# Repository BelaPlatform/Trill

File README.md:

# Trill: Touch Sensing for Makers

Trill sensors are designed to bring beautiful touch interaction to digital projects. Trill sensors are available now on the [Bela Shop](https://shop.bela.io/collections/trill) and via [Mouser Electronics](https://www.mouser.com/c/sensors/sensor-development-tools/?m=Bela).

## Trill libraries and examples

The Bela IDE comes pre-loaded with the [Trill library](https://github.com/BelaPlatform/Bela/tree/master/libraries/Trill) and [Trill examples](https://github.com/BelaPlatform/Bela/tree/master/examples/Trill).

For other platforms:

- [`Trill-Linux`](https://github.com/BelaPlatform/Trill-Linux) contains the Trill library and examples for Linux systems, such as Raspberry Pi

- [`Trill-Arduino`](https://github.com/BelaPlatform/Trill-Arduino) contains the Trill library and examples for Arduino, as well as Arduino-compatible systems such as Teensy. These also include examples of how to connect your Trill sensor to Processing to generate visuals.

## Trill hardware designs

This repo contains the editable PCB designs and manufacturing files for Trill sensors. You can download these schematic source and PCB design files and edit them yourself using [KiCad](https://www.kicad.org/).

### Source Files and Licenses

Trill hardware designs and this datasheet are available under a [Creative Commons Attribution-ShareAlike 4.0 International (CC BY-SA 4.0)](http://creativecommons.org/licenses/by-sa/4.0/) License, meaning they can be freely reused and remixed with attribution, provided modifications remain open source. Trill firmware is licensed under [GNU General Public License 3](https://www.gnu.org/licenses/gpl-3.0.html), meaning that you can freely use, remix, change and extend the code, but you are obligated to make the modified source code available alongside any binaries (flashed, or as files) that you release.

### Commercial Licensing

It's possible to use Trill design files and firmware for a commercial projects free of charge under [CC-BY-SA](http://creativecommons.org/licenses/by-sa/4.0/) (hardware) and [GPL](https://www.gnu.org/licenses/gpl-3.0.en.html) (firmware). Both licenses allow you to use these assets yourself under the license requirements, which include publicly releasing any changes you make to the designs under the same license.

If you want to use Trill design files but not provide attribution and/or not release your source code – for example, because you want to create something to sell using these files but don't want to make your source files public – this is still possible, but requires a commercial license. Augmented Instruments Ltd. can provide you with a commercial license that fits your project and its scope. Get in touch at info@bela.io to discuss your product and the license that's right for you. More information may be found at https://learn.bela.io/products/products-overview/open-source-licenses/#using-trill-in-commercial-products

Please note: The above commercial licensing applies only to modifications to our provided firmware code and PCB designs. You can buy Trill sensors and use them in any commercial or personal project without any additional licensing costs.

## Trill name and logo 

Trill and Bela names and logos are copyright Augmented Instruments Ltd. Any  designs that you release or produce should **not** use the Trill name or logo and/or the Bela name and logo, whether modified or exact copies.

## Datasheet

This repo contains the Trill datasheet. There is one datasheet for all Trill sensors that includes technical diagrams and usage information. 

## Fritzing files

Fritzing parts are available for all Trill sensors, in the [Bela Fritzing repo](https://github.com/belaplatform/fritzing).

## Learn more

The Bela Knowledge Base contains great documentation on using Trill! Visit [learn.bela.io/trill](https://learn.bela.io/trill) for more information, as well as our Get Started Guide.

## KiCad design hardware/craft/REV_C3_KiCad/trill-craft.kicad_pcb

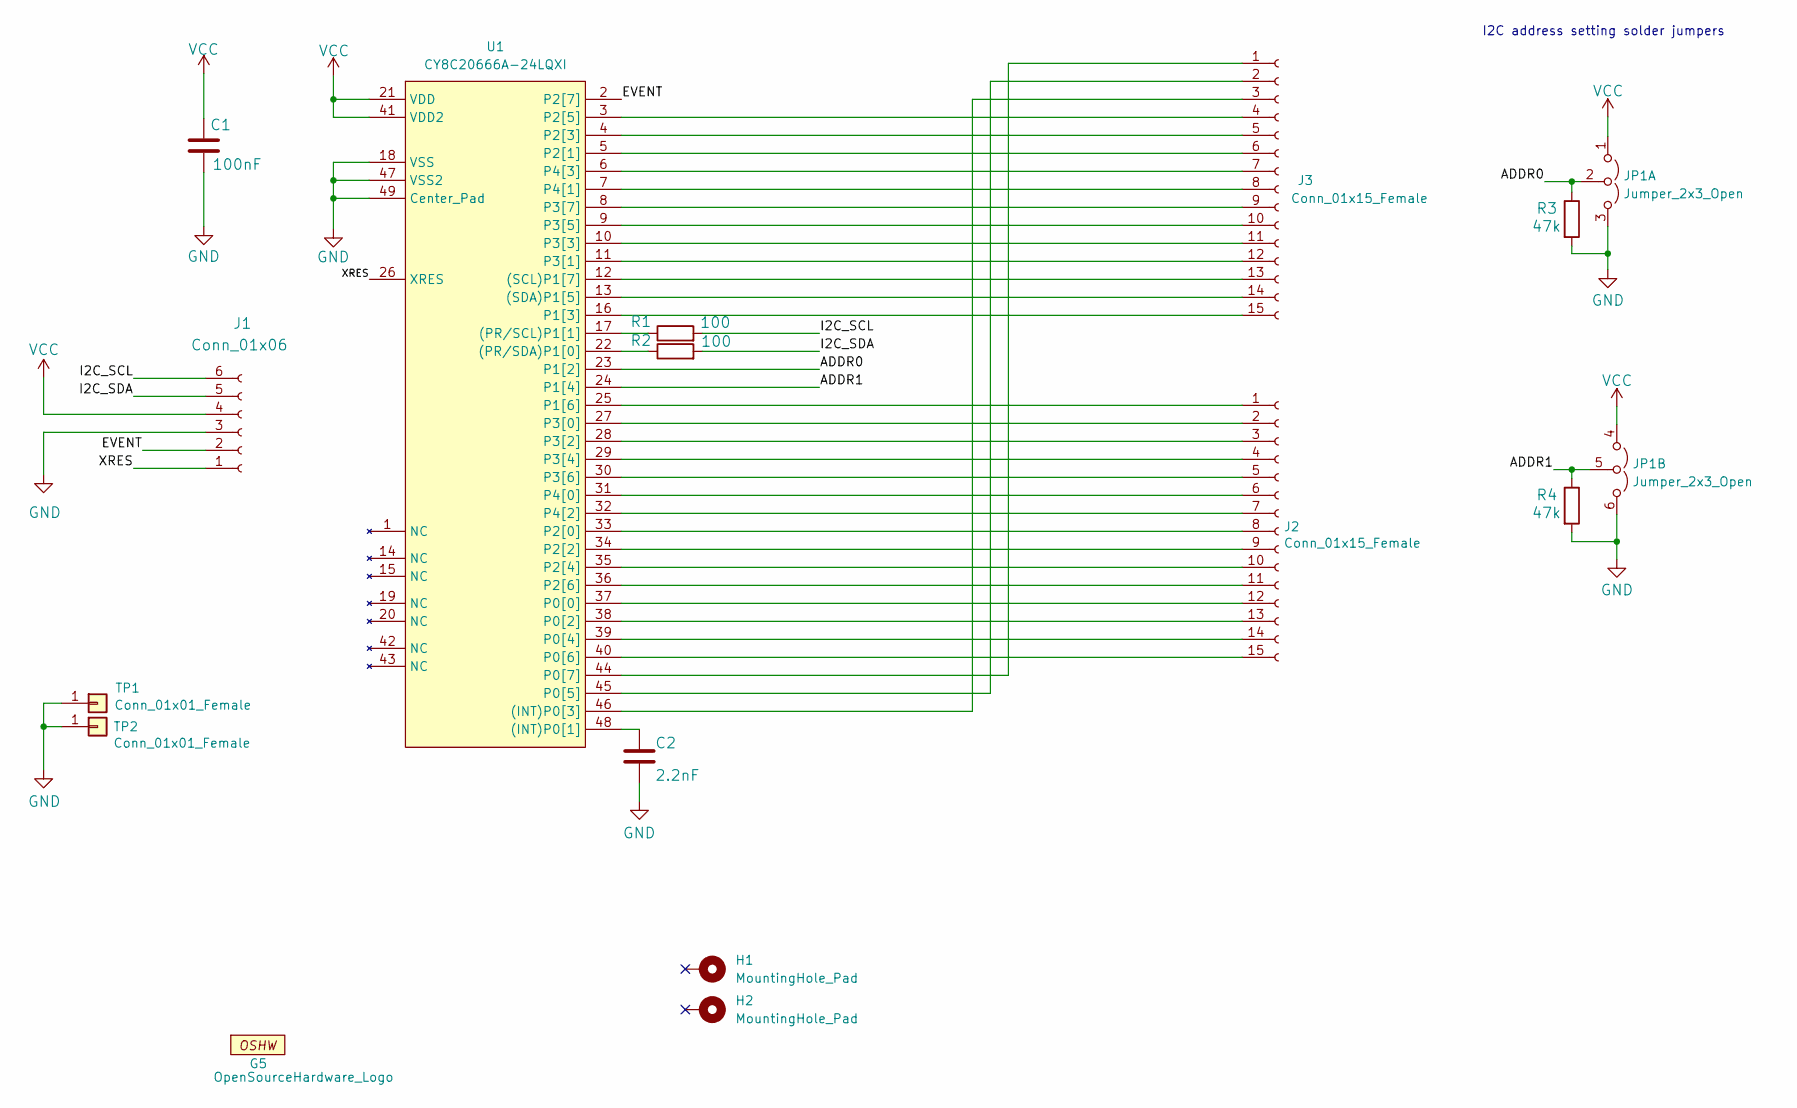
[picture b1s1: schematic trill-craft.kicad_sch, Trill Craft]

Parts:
C1: 100nF; C_0402_1005Metric
C2: 2.2nF; C_0402_1005Metric
G5: OpenSourceHardware_Logo
H1, H2: MountingHole_Pad; MountingHole_3.2mm_M3_ISO14580_Pad
J1: Conn_01x06; trill_craft_1X6_2.54mm_castelated_round
J2, J3: Conn_01x15_Female; trill_craft_1x15_2.54mm_castellated_round
JP1: Jumper_2x3_Open; SolderJumper-2x3_P1.3mm_Open_Pad1.0x1.5mm
R1, R2: 100; R_0402_1005Metric
R3, R4: 47k; R_0402_1005Metric
TP1, TP2: Conn_01x01_Female; trill_craft_circular_pad_smd
U1: CY8C20666A-24LQXI; QFN-48-1EP_6x6mm_P0.4mm_EP4.6x4.6mm

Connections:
/ADDR0: JP1.2 (C), R3.1, U1.23 (P1[2])
/ADDR1: JP1.5 (A), R4.1, U1.24 (P1[4])
/EVENT: J1.2, U1.2 (P2[7])
/I2C_SCL: J1.6, R1.2
/I2C_SDA: J1.5, R2.2
/XRES: J1.1, U1.26 (XRES)
GND: C1.1, C2.2, J1.3, JP1.3 (B), JP1.6 (B), R3.2, R4.2, TP1.1, TP2.1, U1.18 (VSS), U1.47 (VSS2), U1.49 (Center_Pad)
unnamed: J2.1, U1.25 (P1[6])
unnamed: J2.2, U1.27 (P3[0])
unnamed: J2.3, U1.28 (P3[2])
unnamed: J2.4, U1.29 (P3[4])
unnamed: J2.5, U1.30 (P3[6])
unnamed: J2.6, U1.31 (P4[0])
unnamed: J2.7, U1.32 (P4[2])
unnamed: J2.8, U1.33 (P2[0])
unnamed: J2.9, U1.34 (P2[2])
unnamed: J2.10, U1.35 (P2[4])
unnamed: J2.11, U1.36 (P2[6])
unnamed: J2.12, U1.37 (P0[0])
unnamed: J2.13, U1.38 (P0[2])
unnamed: J2.14, U1.39 (P0[4])
unnamed: J2.15, U1.40 (P0[6])
unnamed: J3.1, U1.44 (P0[7])
unnamed: J3.2, U1.45 (P0[5])
unnamed: J3.3, U1.46 ((INT)P0[3])
unnamed: J3.4, U1.3 (P2[5])
unnamed: J3.5, U1.4 (P2[3])
unnamed: J3.6, U1.5 (P2[1])
unnamed: J3.7, U1.6 (P4[3])
unnamed: J3.8, U1.7 (P4[1])
unnamed: J3.9, U1.8 (P3[7])
unnamed: J3.10, U1.9 (P3[5])
unnamed: J3.11, U1.10 (P3[3])
unnamed: J3.12, U1.11 (P3[1])
unnamed: J3.13, U1.12 ((SCL)P1[7])
unnamed: J3.14, U1.13 ((SDA)P1[5])
unnamed: J3.15, U1.16 (P1[3])
unnamed: C2.1, U1.48 ((INT)P0[1])
unnamed: R1.1, U1.17 ((PR/SCL)P1[1])
unnamed: R2.1, U1.22 ((PR/SDA)P1[0])
VCC: C1.2, J1.4, JP1.1 (A), JP1.4 (A), U1.21 (VDD), U1.41 (VDD2)

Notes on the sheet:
I2C address setting solder jumpers

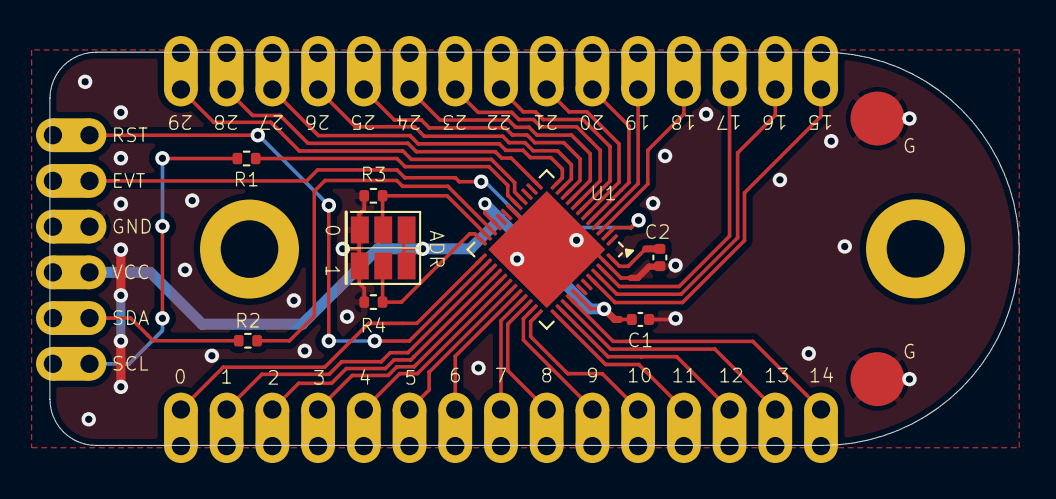
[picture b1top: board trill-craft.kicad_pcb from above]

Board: 2 copper layers, 53.8 x 21.8 mm, 16 parts (1 on the bottom side), 41 nets.

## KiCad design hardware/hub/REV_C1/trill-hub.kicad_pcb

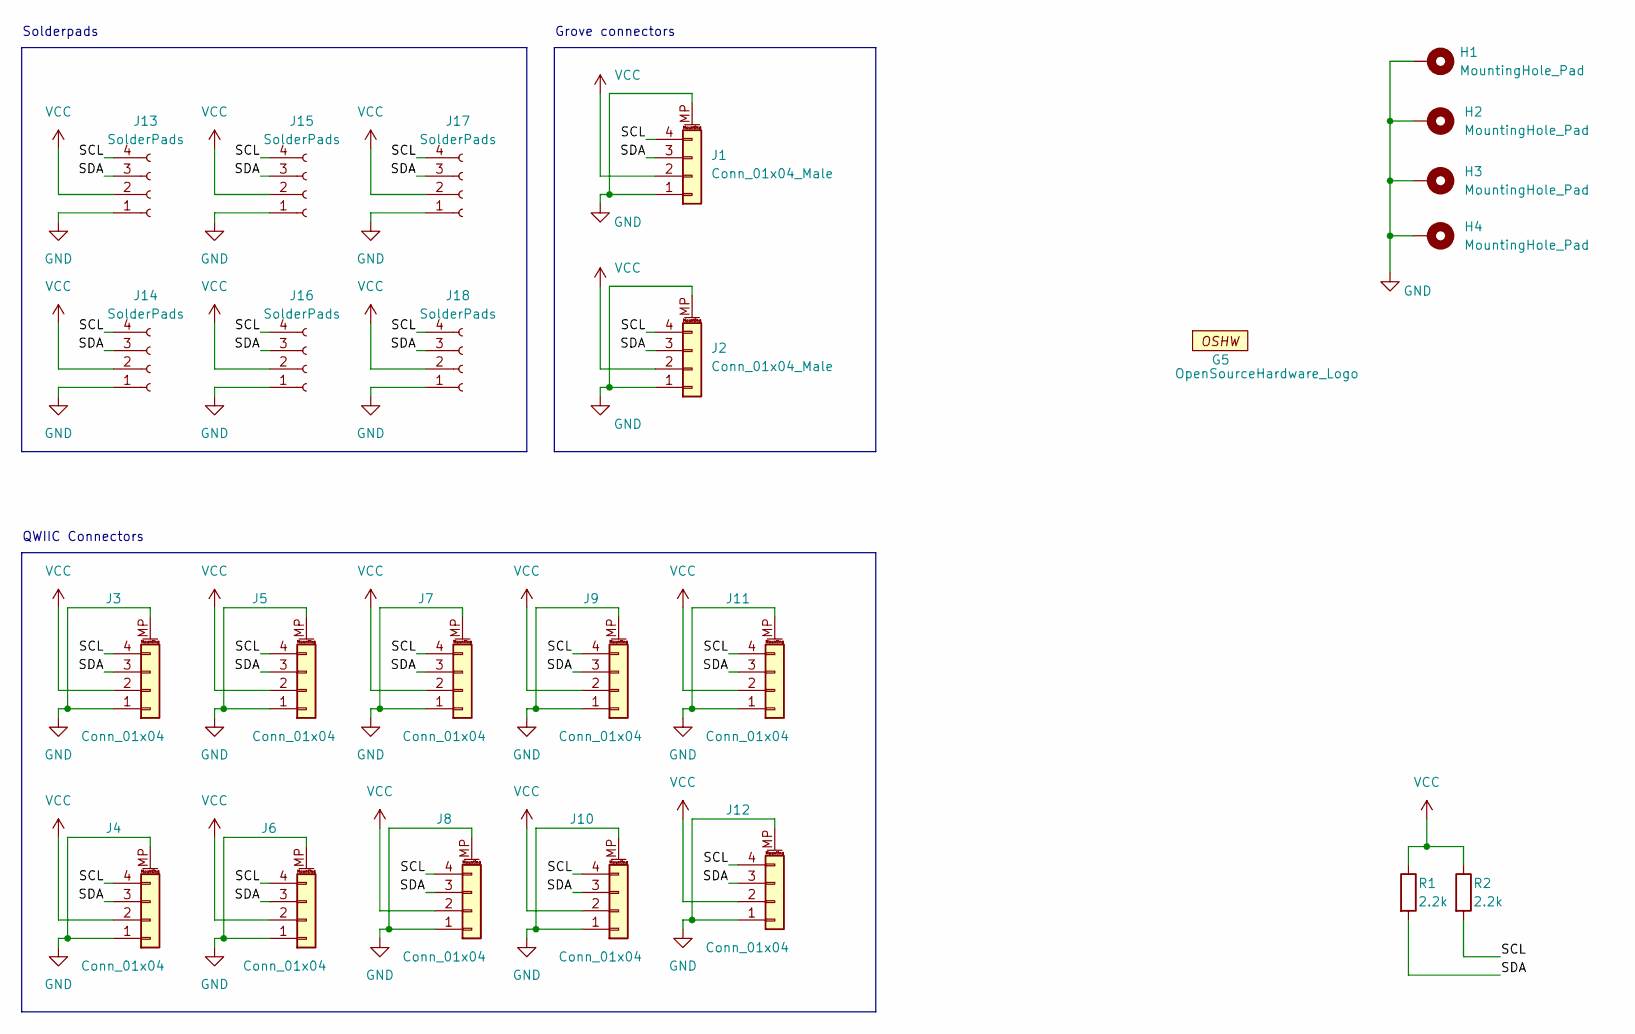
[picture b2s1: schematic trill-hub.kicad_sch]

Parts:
G5: OpenSourceHardware_Logo
H1, H2, H3, H4: MountingHole_Pad; MountingHole_3.2mm_M3_ISO14580_Pad
J1, J2: Conn_01x04_Male; JST_PH_B4B-PH-SM4-TB_1x04-1MP_P2.00mm_Vertical
J3, J4, J5, J6, J7, J8, J9, J10, J11, J12: Conn_01x04; qwiic_vertical_SMD
J13, J14, J15, J16, J17, J18: SolderPads; Connector_1x04_LongPads
R1, R2: 2.2k; R_0402_1005Metric

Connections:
/SCL: J1.4, J2.4, J3.4, J4.4, J5.4, J6.4, J7.4, J8.4, J9.4, J10.4, J11.4, J12.4, J13.4, J14.4, J15.4, J16.4, J17.4, J18.4, R2.2
/SDA: J1.3, J2.3, J3.3, J4.3, J5.3, J6.3, J7.3, J8.3, J9.3, J10.3, J11.3, J12.3, J13.3, J14.3, J15.3, J16.3, J17.3, J18.3, R1.2
GND: H1.1, H2.1, H3.1, H4.1, J1.1, J1.MP (MountPin), J2.1, J2.MP (MountPin), J3.1, J3.MP (MountPin), J4.1, J4.MP (MountPin), J5.1, J5.MP (MountPin), J6.1, J6.MP (MountPin), J7.1, J7.MP (MountPin), J8.1, J8.MP (MountPin), J9.1, J9.MP (MountPin), J10.1, J10.MP (MountPin), J11.1, J11.MP (MountPin), J12.1, J12.MP (MountPin), J13.1, J14.1, J15.1, J16.1, J17.1, J18.1
VCC: J1.2, J2.2, J3.2, J4.2, J5.2, J6.2, J7.2, J8.2, J9.2, J10.2, J11.2, J12.2, J13.2, J14.2, J15.2, J16.2, J17.2, J18.2, R1.1, R2.1

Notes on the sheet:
Solderpads
QWIIC Connectors
Grove connectors

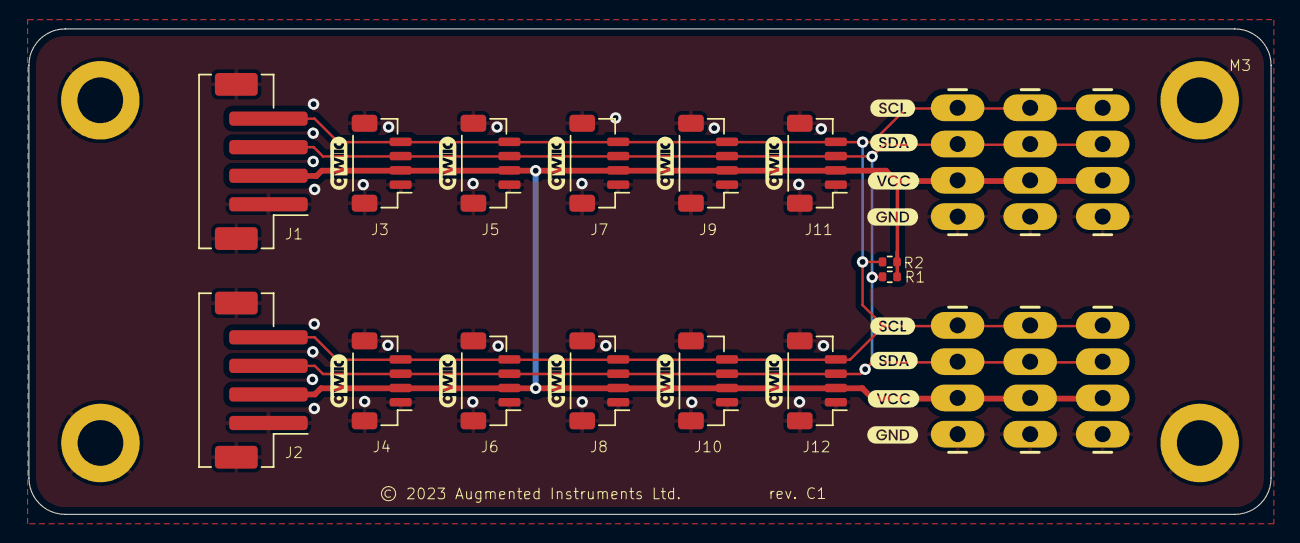
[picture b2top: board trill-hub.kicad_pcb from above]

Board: 2 copper layers, 87.0 x 34.0 mm, 25 parts (1 on the bottom side), 4 nets.

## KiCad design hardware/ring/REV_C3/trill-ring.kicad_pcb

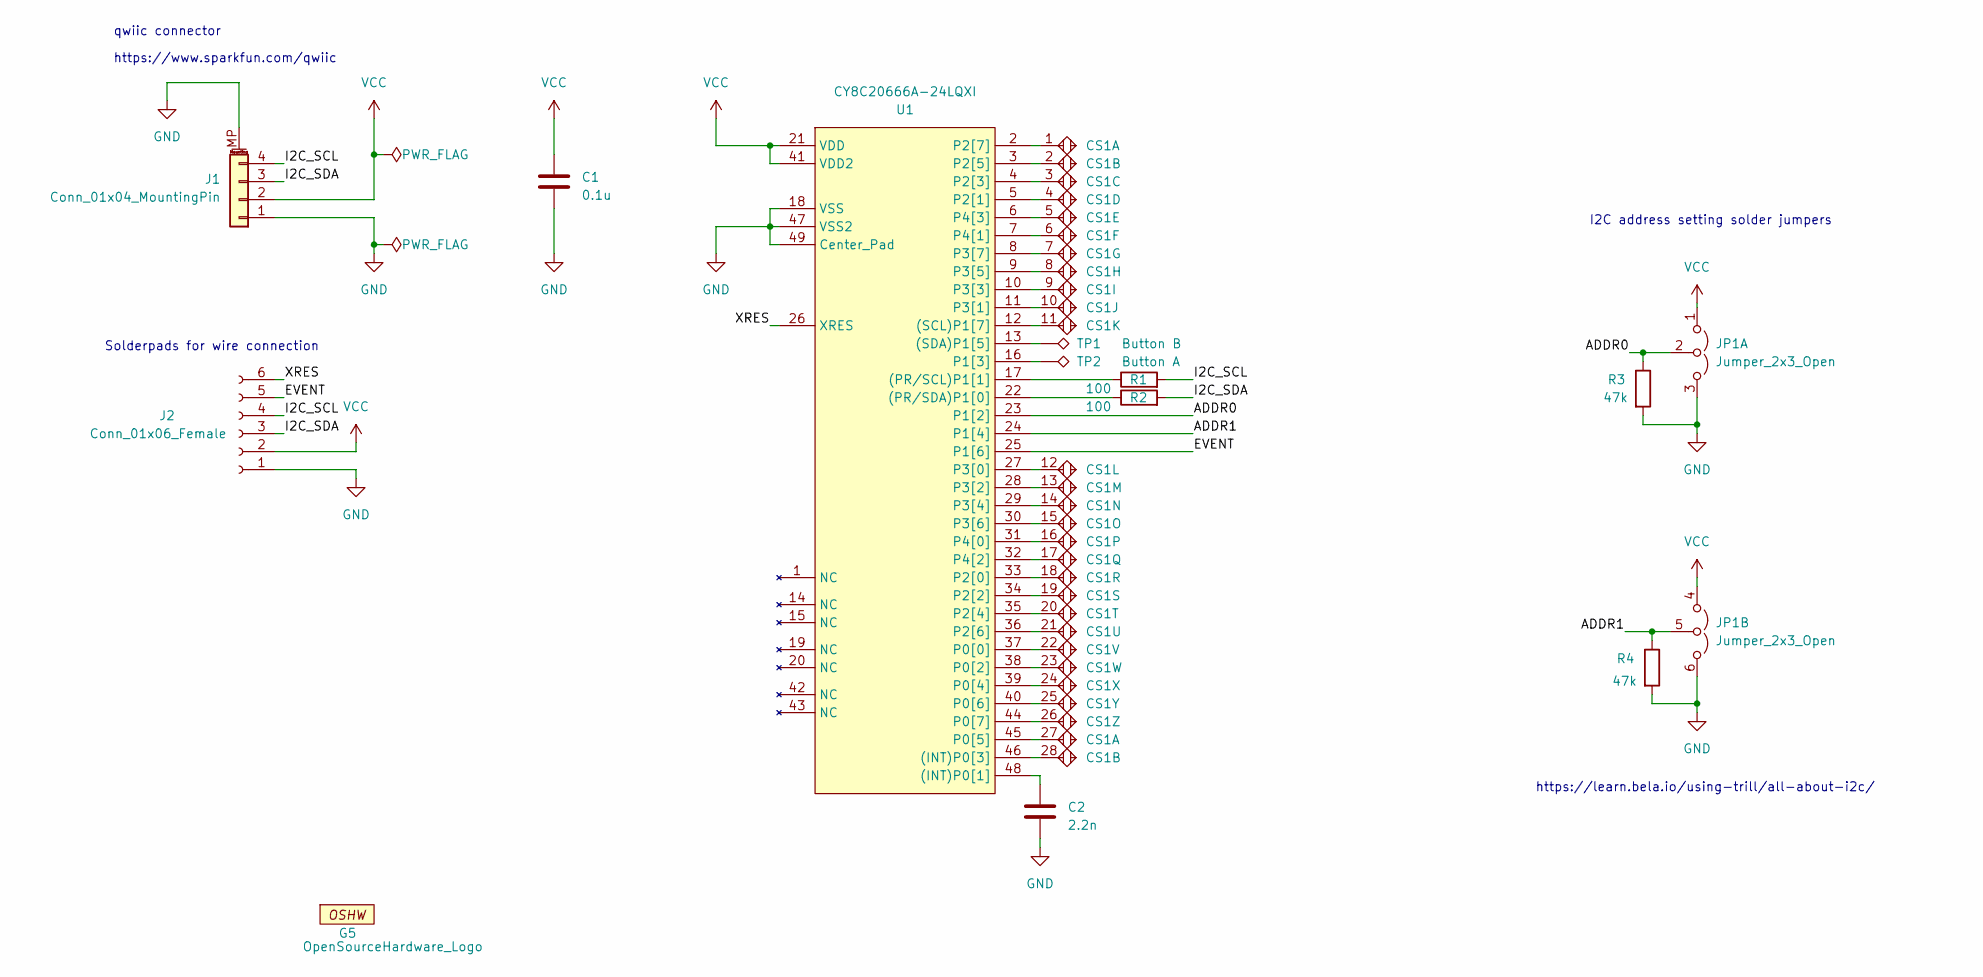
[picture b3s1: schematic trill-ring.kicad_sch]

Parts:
C1: 0.1u; C_0402_1005Metric
C2: 2.2n; C_0402_1005Metric
CS1: TRILL_RING-28_CapSense; TRILL_RING_CapSense
G5: OpenSourceHardware_Logo
J1: Conn_01x04_MountingPin; qwiic_horizontal_SMD
J2: Conn_01x06_Female; I2C+EVT_RST_Wire_connector_SMD
JP1: Jumper_2x3_Open; SolderJumper-2x3_P1.3mm_Open_Pad1.0x1.5mm
R1, R2: 100; R_0402_1005Metric
R3, R4: 47k; R_0402_1005Metric
TP1: Button B; TestPoint_Pad_D2.0mm
TP2: Button A; TestPoint_Pad_D2.0mm
U1: CY8C20666A-24LQXI; QFN-48-1EP_6x6mm_P0.4mm_EP4.6x4.6mm

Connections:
/ADDR0: JP1.2 (C), R3.1, U1.23 (P1[2])
/ADDR1: JP1.5 (A), R4.1, U1.24 (P1[4])
/EVENT: J2.5, U1.25 (P1[6])
/I2C_SCL: J1.4, J2.4, R1.2
/I2C_SDA: J1.3, J2.3, R2.2
/XRES: J2.6, U1.26 (XRES)
GND: C1.2, C2.2, J1.1, J1.MP (MountPin), J2.1, JP1.3 (B), JP1.6 (B), R3.2, R4.2, U1.18 (VSS), U1.47 (VSS2), U1.49 (Center_Pad)
unnamed: C2.1, U1.48 ((INT)P0[1])
unnamed: CS1.28, U1.46 ((INT)P0[3])
unnamed: R1.1, U1.17 ((PR/SCL)P1[1])
unnamed: R2.1, U1.22 ((PR/SDA)P1[0])
unnamed: CS1.11, U1.12 ((SCL)P1[7])
unnamed: TP1.1, U1.13 ((SDA)P1[5])
unnamed: CS1.22, U1.37 (P0[0])
unnamed: CS1.23, U1.38 (P0[2])
unnamed: CS1.24, U1.39 (P0[4])
unnamed: CS1.27, U1.45 (P0[5])
unnamed: CS1.25, U1.40 (P0[6])
unnamed: CS1.26, U1.44 (P0[7])
unnamed: TP2.1, U1.16 (P1[3])
unnamed: CS1.18, U1.33 (P2[0])
unnamed: CS1.4, U1.5 (P2[1])
unnamed: CS1.19, U1.34 (P2[2])
unnamed: CS1.3, U1.4 (P2[3])
unnamed: CS1.20, U1.35 (P2[4])
unnamed: CS1.2, U1.3 (P2[5])
unnamed: CS1.21, U1.36 (P2[6])
unnamed: CS1.1, U1.2 (P2[7])
unnamed: CS1.12, U1.27 (P3[0])
unnamed: CS1.10, U1.11 (P3[1])
unnamed: CS1.13, U1.28 (P3[2])
unnamed: CS1.9, U1.10 (P3[3])
unnamed: CS1.14, U1.29 (P3[4])
unnamed: CS1.8, U1.9 (P3[5])
unnamed: CS1.15, U1.30 (P3[6])
unnamed: CS1.7, U1.8 (P3[7])
unnamed: CS1.16, U1.31 (P4[0])
unnamed: CS1.6, U1.7 (P4[1])
unnamed: CS1.17, U1.32 (P4[2])
unnamed: CS1.5, U1.6 (P4[3])
VCC: C1.1, J1.2, J2.2, JP1.1 (A), JP1.4 (A), U1.21 (VDD), U1.41 (VDD2)

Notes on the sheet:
I2C address setting solder jumpers
qwiic connector
Solderpads for wire connection
https://learn.bela.io/using-trill/all-about-i2c/
https://www.sparkfun.com/qwiic

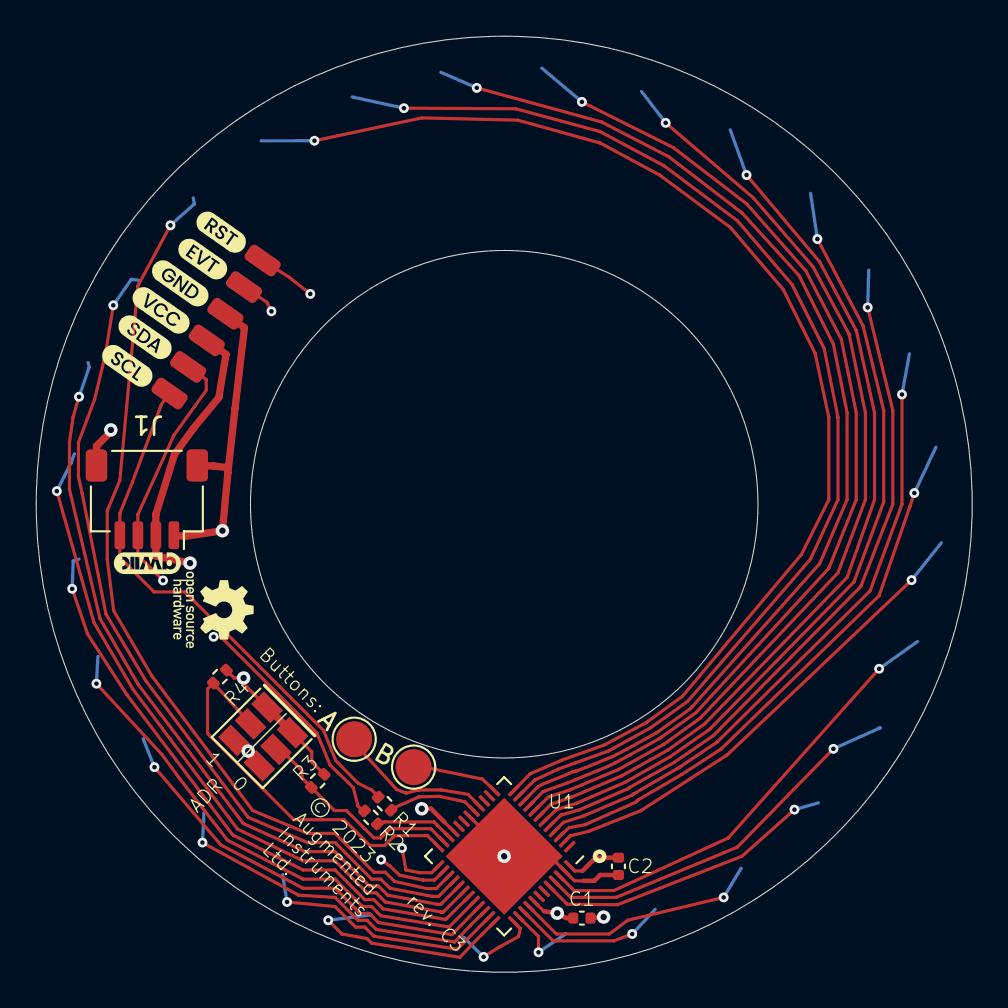
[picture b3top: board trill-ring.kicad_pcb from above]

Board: 4 copper layers, 52.0 x 52.0 mm, 14 parts (0 on the bottom side), 41 nets.

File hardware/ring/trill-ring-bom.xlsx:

Name | Quantity | Value | Package | Description | Mouser # | Digi-Key # | Datasheet / Notes
C1 | 1 | 0.1uF | “0402" | Capacitor ceramic 0402; standard bypass cap 5V+
C2 | 1 | 2.2nF | “0402" | Capacitor ceramic 0402; 5% | 81-GRM36X222J50
IC1 | 1 | CY8C20636A-24LTXI | 48-QFN, 7x7mm | IC Cypress SoC | 727-CY8C20636A24LTXI
J1 | 1 | Grove connector, vertical SMT | SMD | 4-pin 2mm vertical Grove connector (Seeed)
R1-R2 | 2 | 100 ohm | “0402" | Resistor 0603 (standard part)
R3-R4 | 2 | 47k ohm | “0402" | Resistor 0603 (standard part)
Total | 8

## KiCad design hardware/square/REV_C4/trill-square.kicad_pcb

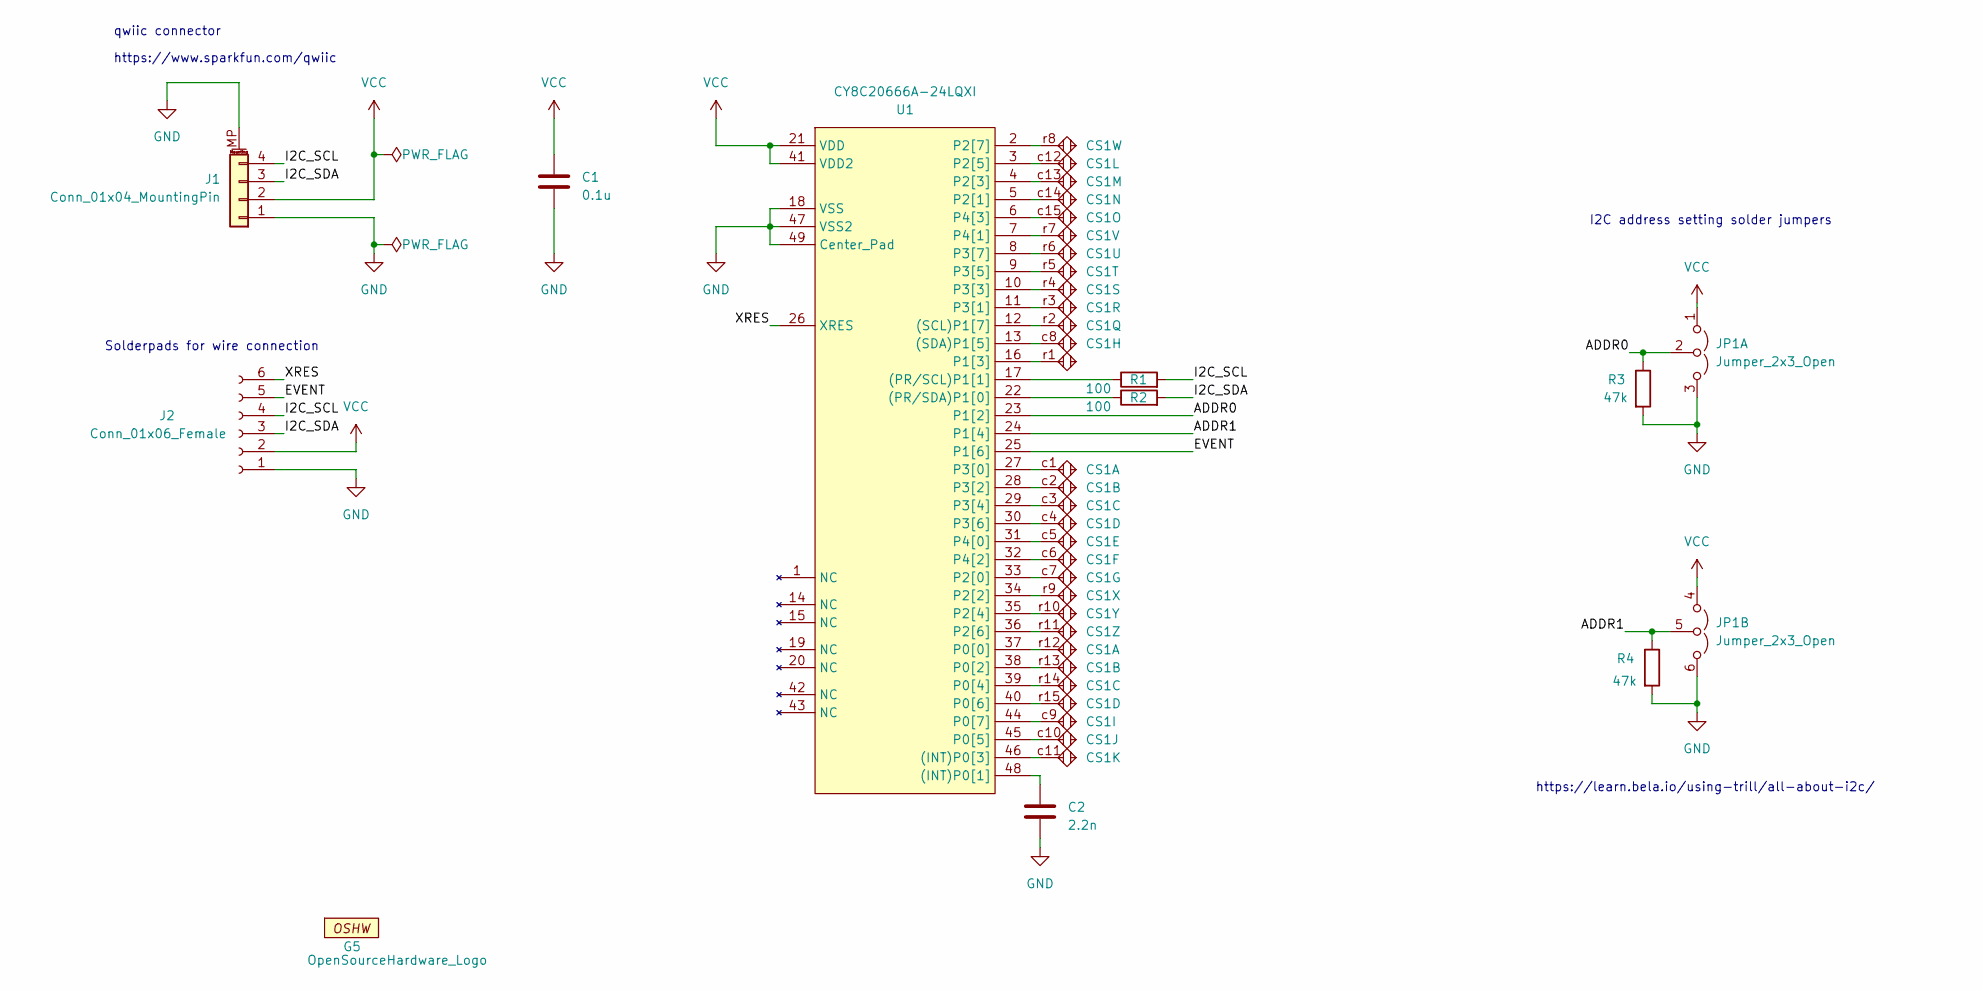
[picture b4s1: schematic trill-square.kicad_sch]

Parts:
C1: 0.1u; C_0402_1005Metric
C2: 2.2n; C_0402_1005Metric
CS1: CapSensePad; TRILL_SQUARE_CapSense
G5: OpenSourceHardware_Logo
J1: Conn_01x04_MountingPin; qwiic_horizontal_SMD
J2: Conn_01x06_Female; I2C+EVT_RST_Wire_connector_SMD
JP1: Jumper_2x3_Open; SolderJumper-2x3_P1.3mm_Open_Pad1.0x1.5mm
R1, R2: 100; R_0402_1005Metric
R3, R4: 47k; R_0402_1005Metric
U1: CY8C20666A-24LQXI; QFN-48-1EP_6x6mm_P0.4mm_EP4.6x4.6mm

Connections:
/ADDR0: JP1.2 (C), R3.1, U1.23 (P1[2])
/ADDR1: JP1.5 (A), R4.1, U1.24 (P1[4])
/EVENT: J2.5, U1.25 (P1[6])
/I2C_SCL: J1.4, J2.4, R1.2
/I2C_SDA: J1.3, J2.3, R2.2
/XRES: J2.6, U1.26 (XRES)
GND: C1.2, C2.2, J1.1, J1.MP (MountPin), J2.1, JP1.3 (B), JP1.6 (B), R3.2, R4.2, U1.18 (VSS), U1.47 (VSS2), U1.49 (Center_Pad)
unnamed: C2.1, U1.48 ((INT)P0[1])
unnamed: CS1.c11, U1.46 ((INT)P0[3])
unnamed: R1.1, U1.17 ((PR/SCL)P1[1])
unnamed: R2.1, U1.22 ((PR/SDA)P1[0])
unnamed: CS1.r2, U1.12 ((SCL)P1[7])
unnamed: CS1.c8, U1.13 ((SDA)P1[5])
unnamed: CS1.r12, U1.37 (P0[0])
unnamed: CS1.r13, U1.38 (P0[2])
unnamed: CS1.r14, U1.39 (P0[4])
unnamed: CS1.c10, U1.45 (P0[5])
unnamed: CS1.r15, U1.40 (P0[6])
unnamed: CS1.c9, U1.44 (P0[7])
unnamed: CS1.r1, U1.16 (P1[3])
unnamed: CS1.c7, U1.33 (P2[0])
unnamed: CS1.c14, U1.5 (P2[1])
unnamed: CS1.r9, U1.34 (P2[2])
unnamed: CS1.c13, U1.4 (P2[3])
unnamed: CS1.r10, U1.35 (P2[4])
unnamed: CS1.c12, U1.3 (P2[5])
unnamed: CS1.r11, U1.36 (P2[6])
unnamed: CS1.r8, U1.2 (P2[7])
unnamed: CS1.c1, U1.27 (P3[0])
unnamed: CS1.r3, U1.11 (P3[1])
unnamed: CS1.c2, U1.28 (P3[2])
unnamed: CS1.r4, U1.10 (P3[3])
unnamed: CS1.c3, U1.29 (P3[4])
unnamed: CS1.r5, U1.9 (P3[5])
unnamed: CS1.c4, U1.30 (P3[6])
unnamed: CS1.r6, U1.8 (P3[7])
unnamed: CS1.c5, U1.31 (P4[0])
unnamed: CS1.r7, U1.7 (P4[1])
unnamed: CS1.c6, U1.32 (P4[2])
unnamed: CS1.c15, U1.6 (P4[3])
VCC: C1.1, J1.2, J2.2, JP1.1 (A), JP1.4 (A), U1.21 (VDD), U1.41 (VDD2)

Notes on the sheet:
Solderpads for wire connection
qwiic connector
https://www.sparkfun.com/qwiic
https://learn.bela.io/using-trill/all-about-i2c/
I2C address setting solder jumpers

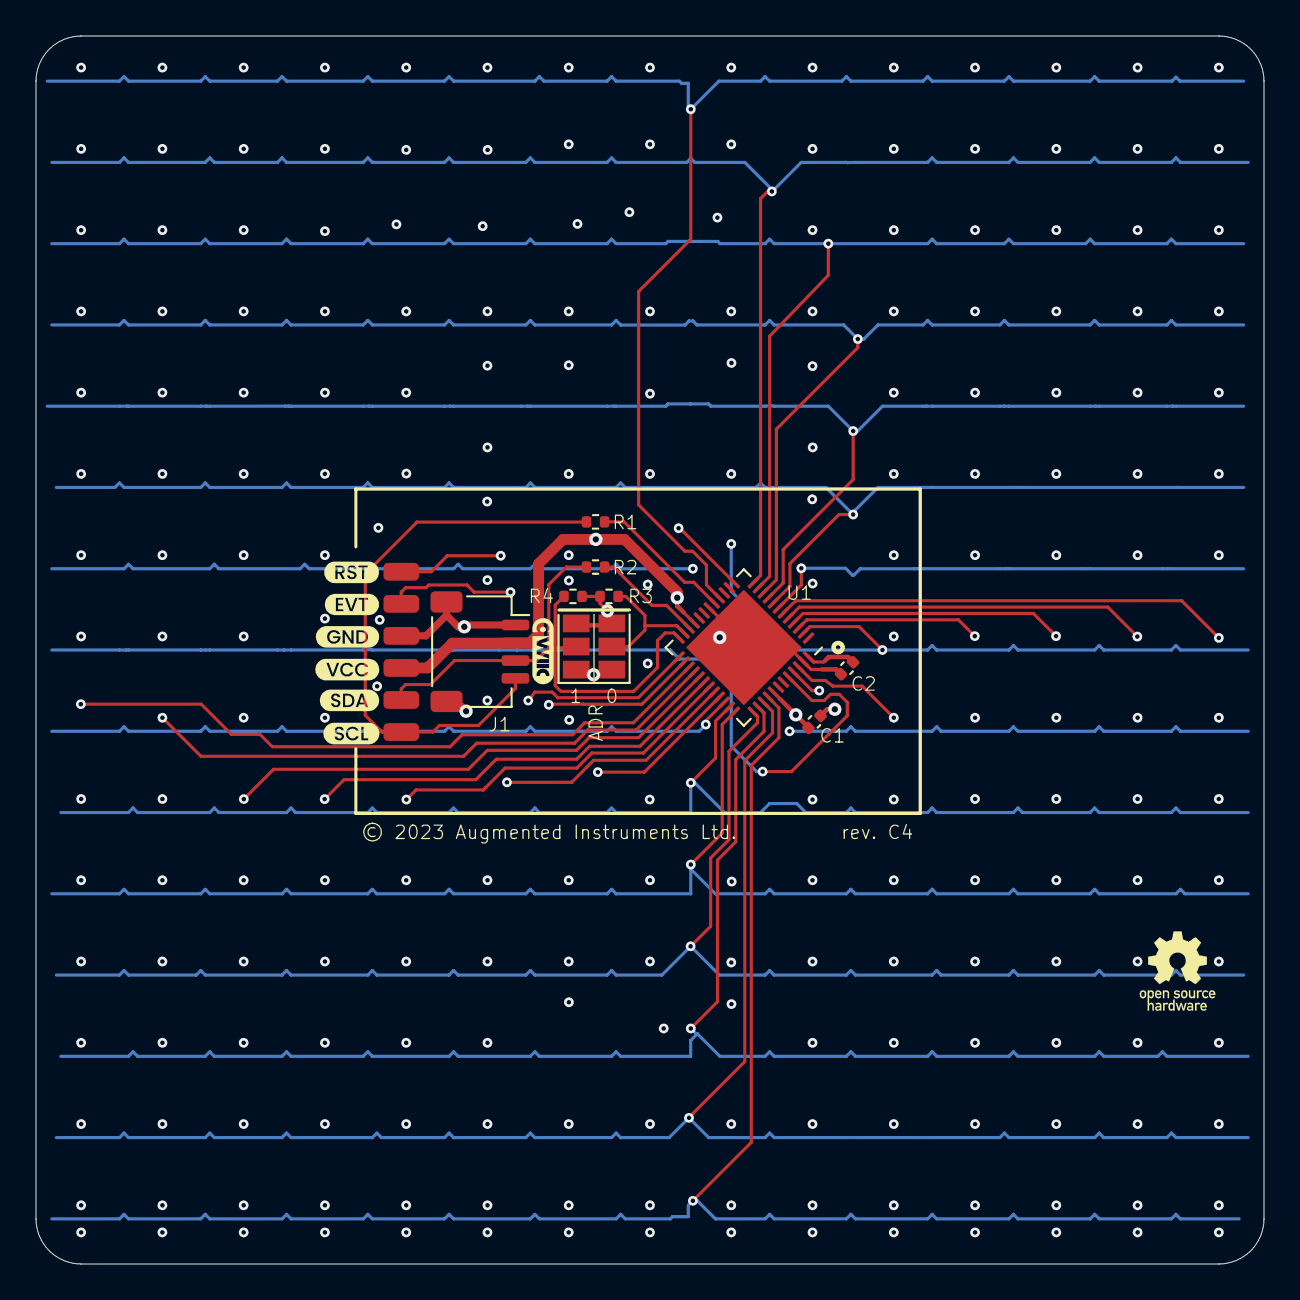
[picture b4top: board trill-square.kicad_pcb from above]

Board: 4 copper layers, 69.1 x 69.1 mm, 12 parts (0 on the bottom side), 41 nets.

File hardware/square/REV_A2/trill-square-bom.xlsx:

Name | Quantity | Value | Package | Description | Mouser # | Digi-Key # | Datasheet / Notes
C1 | 1 | 0.1uF | “0402" | Capacitor ceramic 0402; standard bypass cap 5V+
C2 | 1 | 2.2nF | “0402" | Capacitor ceramic 0402; 5% | 81-GRM36X222J50
IC1 | 1 | CY8C20636A-24LTXI | 48-QFN, 7x7mm | IC Cypress SoC | 727-CY8C20636A24LTXI
J1 | 1 | Grove connector, vertical SMT | SMD | 4-pin 2mm vertical Grove connector (Seeed)
R1-R2 | 2 | 100 ohm | “0402" | Resistor 0603 (standard part)
R3-R4 | 2 | 47k ohm | “0402" | Resistor 0603 (standard part)
Total | 8

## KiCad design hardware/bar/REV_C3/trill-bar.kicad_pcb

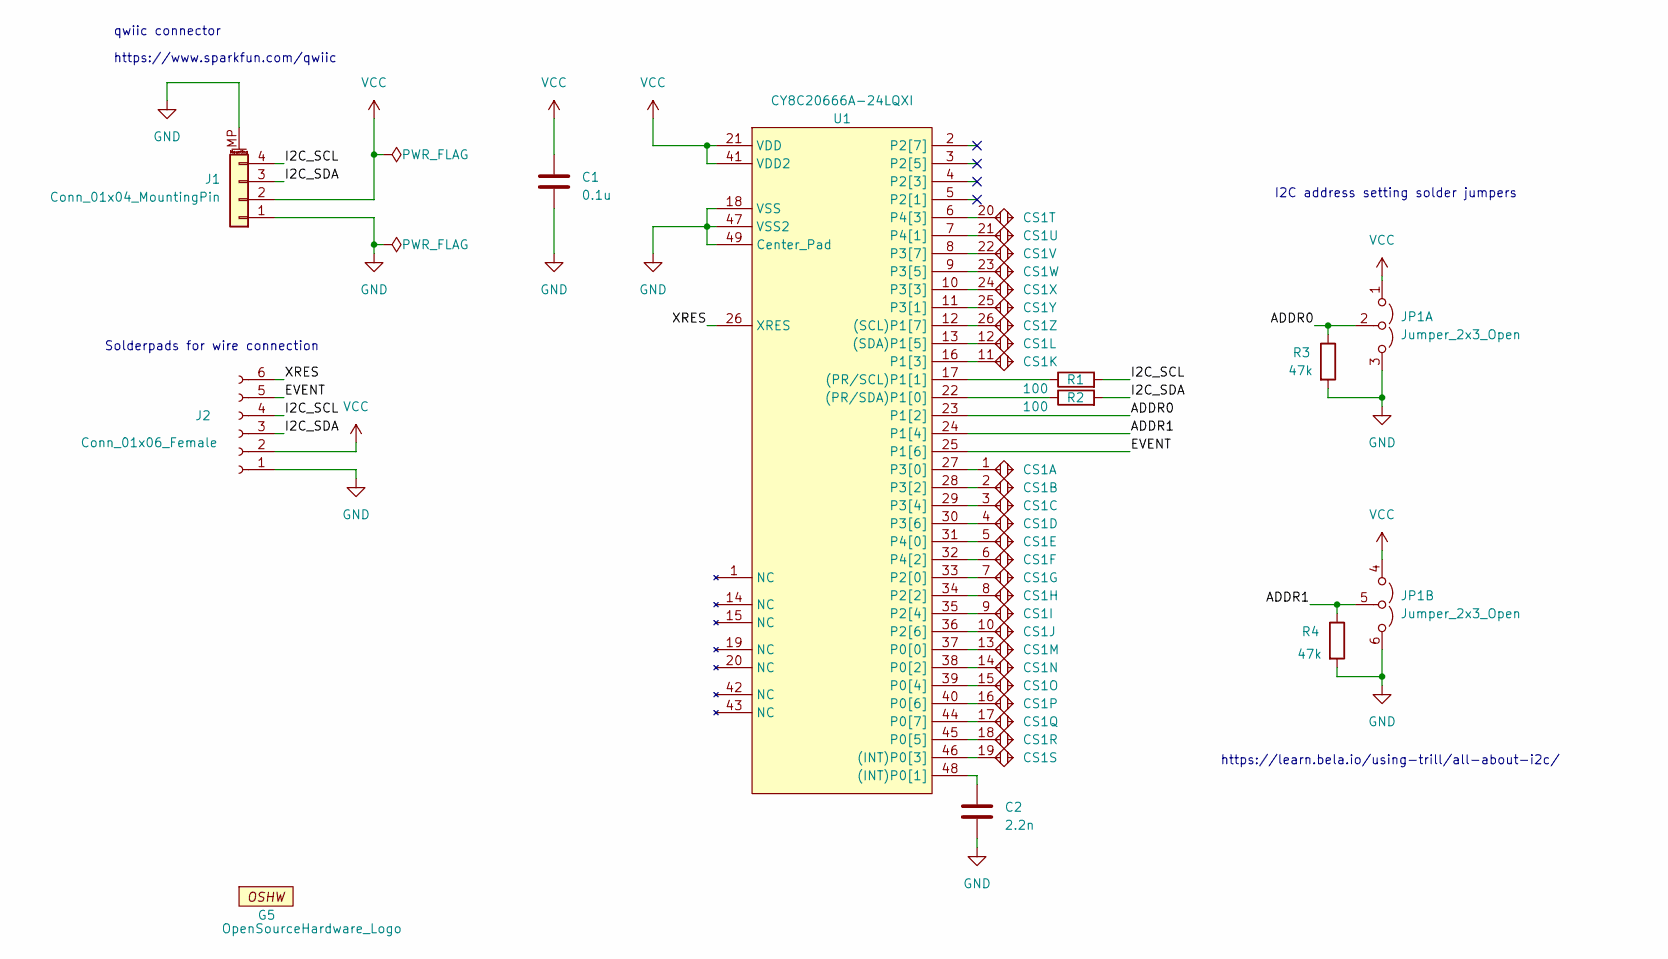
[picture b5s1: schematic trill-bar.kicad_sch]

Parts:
C1: 0.1u; C_0402_1005Metric
C2: 2.2n; C_0402_1005Metric
CS1: TRILL_BAR-26_CapSense; TRILL_BAR_CapSense
G5: OpenSourceHardware_Logo
J1: Conn_01x04_MountingPin; qwiic_horizontal_SMD
J2: Conn_01x06_Female; I2C+EVT_RST_Wire_connector_SMD
JP1: Jumper_2x3_Open; SolderJumper-2x3_P1.3mm_Open_Pad1.0x1.5mm
R1, R2: 100; R_0402_1005Metric
R3, R4: 47k; R_0402_1005Metric
U1: CY8C20666A-24LQXI; QFN-48-1EP_6x6mm_P0.4mm_EP4.6x4.6mm

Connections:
/ADDR0: JP1.2 (C), R3.1, U1.23 (P1[2])
/ADDR1: JP1.5 (A), R4.1, U1.24 (P1[4])
/EVENT: J2.5, U1.25 (P1[6])
/I2C_SCL: J1.4, J2.4, R1.2
/I2C_SDA: J1.3, J2.3, R2.2
/XRES: J2.6, U1.26 (XRES)
GND: C1.2, C2.2, J1.1, J1.MP (MountPin), J2.1, JP1.3 (B), JP1.6 (B), R3.2, R4.2, U1.18 (VSS), U1.47 (VSS2), U1.49 (Center_Pad)
unnamed: C2.1, U1.48 ((INT)P0[1])
unnamed: CS1.19, U1.46 ((INT)P0[3])
unnamed: R1.1, U1.17 ((PR/SCL)P1[1])
unnamed: R2.1, U1.22 ((PR/SDA)P1[0])
unnamed: CS1.26, U1.12 ((SCL)P1[7])
unnamed: CS1.12, U1.13 ((SDA)P1[5])
unnamed: CS1.13, U1.37 (P0[0])
unnamed: CS1.14, U1.38 (P0[2])
unnamed: CS1.15, U1.39 (P0[4])
unnamed: CS1.18, U1.45 (P0[5])
unnamed: CS1.16, U1.40 (P0[6])
unnamed: CS1.17, U1.44 (P0[7])
unnamed: CS1.11, U1.16 (P1[3])
unnamed: CS1.7, U1.33 (P2[0])
unnamed: CS1.8, U1.34 (P2[2])
unnamed: CS1.9, U1.35 (P2[4])
unnamed: CS1.10, U1.36 (P2[6])
unnamed: CS1.1, U1.27 (P3[0])
unnamed: CS1.25, U1.11 (P3[1])
unnamed: CS1.2, U1.28 (P3[2])
unnamed: CS1.24, U1.10 (P3[3])
unnamed: CS1.3, U1.29 (P3[4])
unnamed: CS1.23, U1.9 (P3[5])
unnamed: CS1.4, U1.30 (P3[6])
unnamed: CS1.22, U1.8 (P3[7])
unnamed: CS1.5, U1.31 (P4[0])
unnamed: CS1.21, U1.7 (P4[1])
unnamed: CS1.6, U1.32 (P4[2])
unnamed: CS1.20, U1.6 (P4[3])
VCC: C1.1, J1.2, J2.2, JP1.1 (A), JP1.4 (A), U1.21 (VDD), U1.41 (VDD2)

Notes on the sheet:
qwiic connector
I2C address setting solder jumpers
Solderpads for wire connection
https://learn.bela.io/using-trill/all-about-i2c/
https://www.sparkfun.com/qwiic

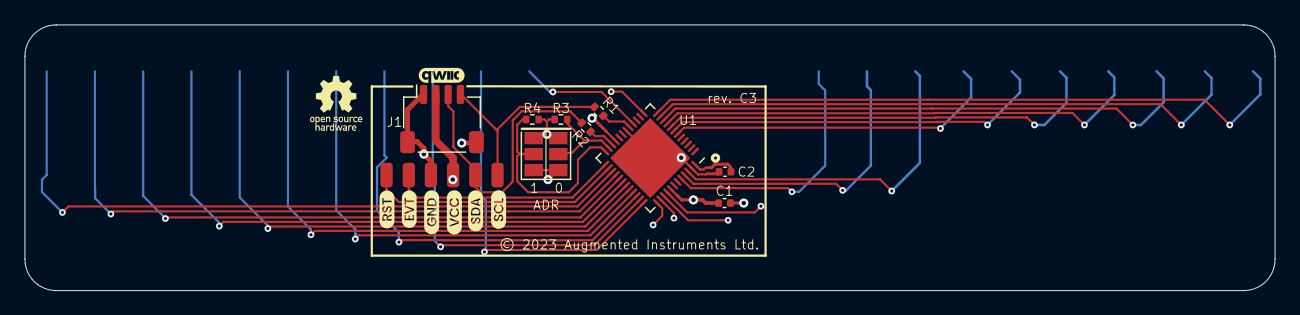
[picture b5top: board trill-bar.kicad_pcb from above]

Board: 4 copper layers, 101.6 x 21.6 mm, 12 parts (0 on the bottom side), 37 nets.

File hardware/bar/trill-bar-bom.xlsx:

Name | Quantity | Value | Package | Description | Mouser # | Digi-Key # | Datasheet / Notes
C1 | 1 | 0.1uF | “0402" | Capacitor ceramic 0402; standard bypass cap 5V+
C2 | 1 | 2.2nF | “0402" | Capacitor ceramic 0402; 5% | 81-GRM36X222J50
IC1 | 1 | CY8C20636A-24LTXI | 48-QFN, 7x7mm | IC Cypress SoC | 727-CY8C20636A24LTXI
J1 | 1 | Grove connector, vertical SMT | SMD | 4-pin 2mm vertical Grove connector (Seeed)
R1-R2 | 2 | 100 ohm | “0402" | Resistor 0603 (standard part)
R3-R4 | 2 | 47k ohm | “0402" | Resistor 0603 (standard part)
Total | 8

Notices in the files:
firmware/common/trill-main.h:
(c) 2020 Augmented Instruments Ltd
These materials are licensed under the Creative Commons BY-SA-NC 4.0:
Attribution, ShareAlike, Non-Commercial. For further information please
hardware/bar/REV_C3/trill-bar.kicad_pcb:
© 2023 Augmented Instruments Ltd.
hardware/craft/REV_C3_KiCad/trill-craft.kicad_pcb:
© 2023
